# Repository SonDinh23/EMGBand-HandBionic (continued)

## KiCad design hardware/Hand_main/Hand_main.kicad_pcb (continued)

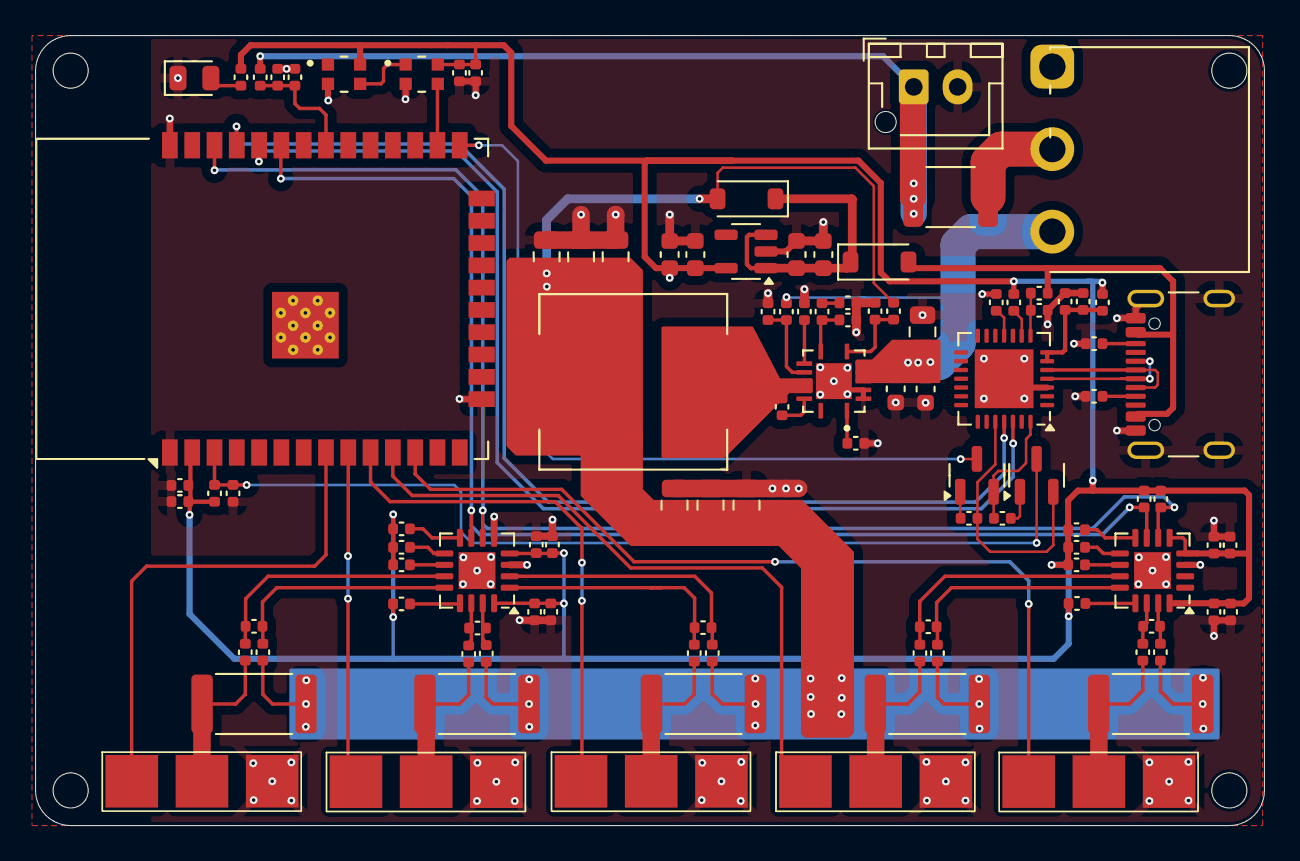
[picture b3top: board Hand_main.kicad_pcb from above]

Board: 4 copper layers, 70.0 x 45.0 mm, 105 parts (0 on the bottom side), 66 nets.

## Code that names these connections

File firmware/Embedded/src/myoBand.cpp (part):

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#define DEBUG
#define WDT_TIMEOUT   120

#define SPI_CS    	15 		   // SPI slave select
#define ADC_CLK     8000000  // SPI clock 1.6MHz

#define PIN_LDO_CE      27
#define PIN_BUTTON      35

#define PIN_CHARGER     34
#define PIN_STD_BAT     36
#define PIN_CHR_BAT     37
#define PIN_BAT         38

#define PIN_BITMASK     0x400000000 // 2^33 in hex

#define PIN_RGB           4
#define PIN_LED_EN        32

#define PIN_MIC_EN        5

#define TIME_WAKEUP   1500
#define BATTERY_MAX   4150
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  Serial.println("Myoband version 0.1");
  gpio_deep_sleep_hold_dis();

  pinMode(PIN_LED_EN, OUTPUT);
  digitalWrite(PIN_LED_EN, HIGH);
	pinMode(PIN_LDO_CE, OUTPUT);
	digitalWrite(PIN_LDO_CE, HIGH);

  pinMode(SPI_CS, OUTPUT);
  digitalWrite(SPI_CS, HIGH);

  pinMode(PIN_BUTTON, INPUT);
  pinMode(PIN_CHARGER, INPUT_PULLDOWN);
  pinMode(PIN_CHR_BAT, INPUT_PULLUP);
  pinMode(PIN_STD_BAT, INPUT_PULLUP);
  
  buzzer.begin();
  // buzzer.offBuzzer();
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  Serial.println("On deep sleep");
  esp_task_wdt_reset();

  digitalWrite(PIN_LED_EN, HIGH);
  pixels.setPixelColor(0, pixels.Color(255, 0 , 0));
  pixels.show();
  vTaskDelay(250);
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  pixels.clear();
  pixels.show();

  digitalWrite(PIN_LED_EN, LOW);
  digitalWrite(PIN_LDO_CE, LOW);
  buzzer.offBuzzer();

  gpio_deep_sleep_hold_en();  
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
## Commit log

2025-12-18 feature: Adjust the directory management system
2025-12-18 feature: Add some 3D images and actual photos of the product
2025-12-18 feature: additional drawing hardware and add information to the hardware Readme file
2025-12-20 feature: additional firmware | fix: added some content to the readme file
2025-12-20 feature: additional App
2025-12-20 fix: added some content to the readme file
